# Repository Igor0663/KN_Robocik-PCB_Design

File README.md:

# KN_Robocik-PCB_Design
PCB projects and circuit schematics

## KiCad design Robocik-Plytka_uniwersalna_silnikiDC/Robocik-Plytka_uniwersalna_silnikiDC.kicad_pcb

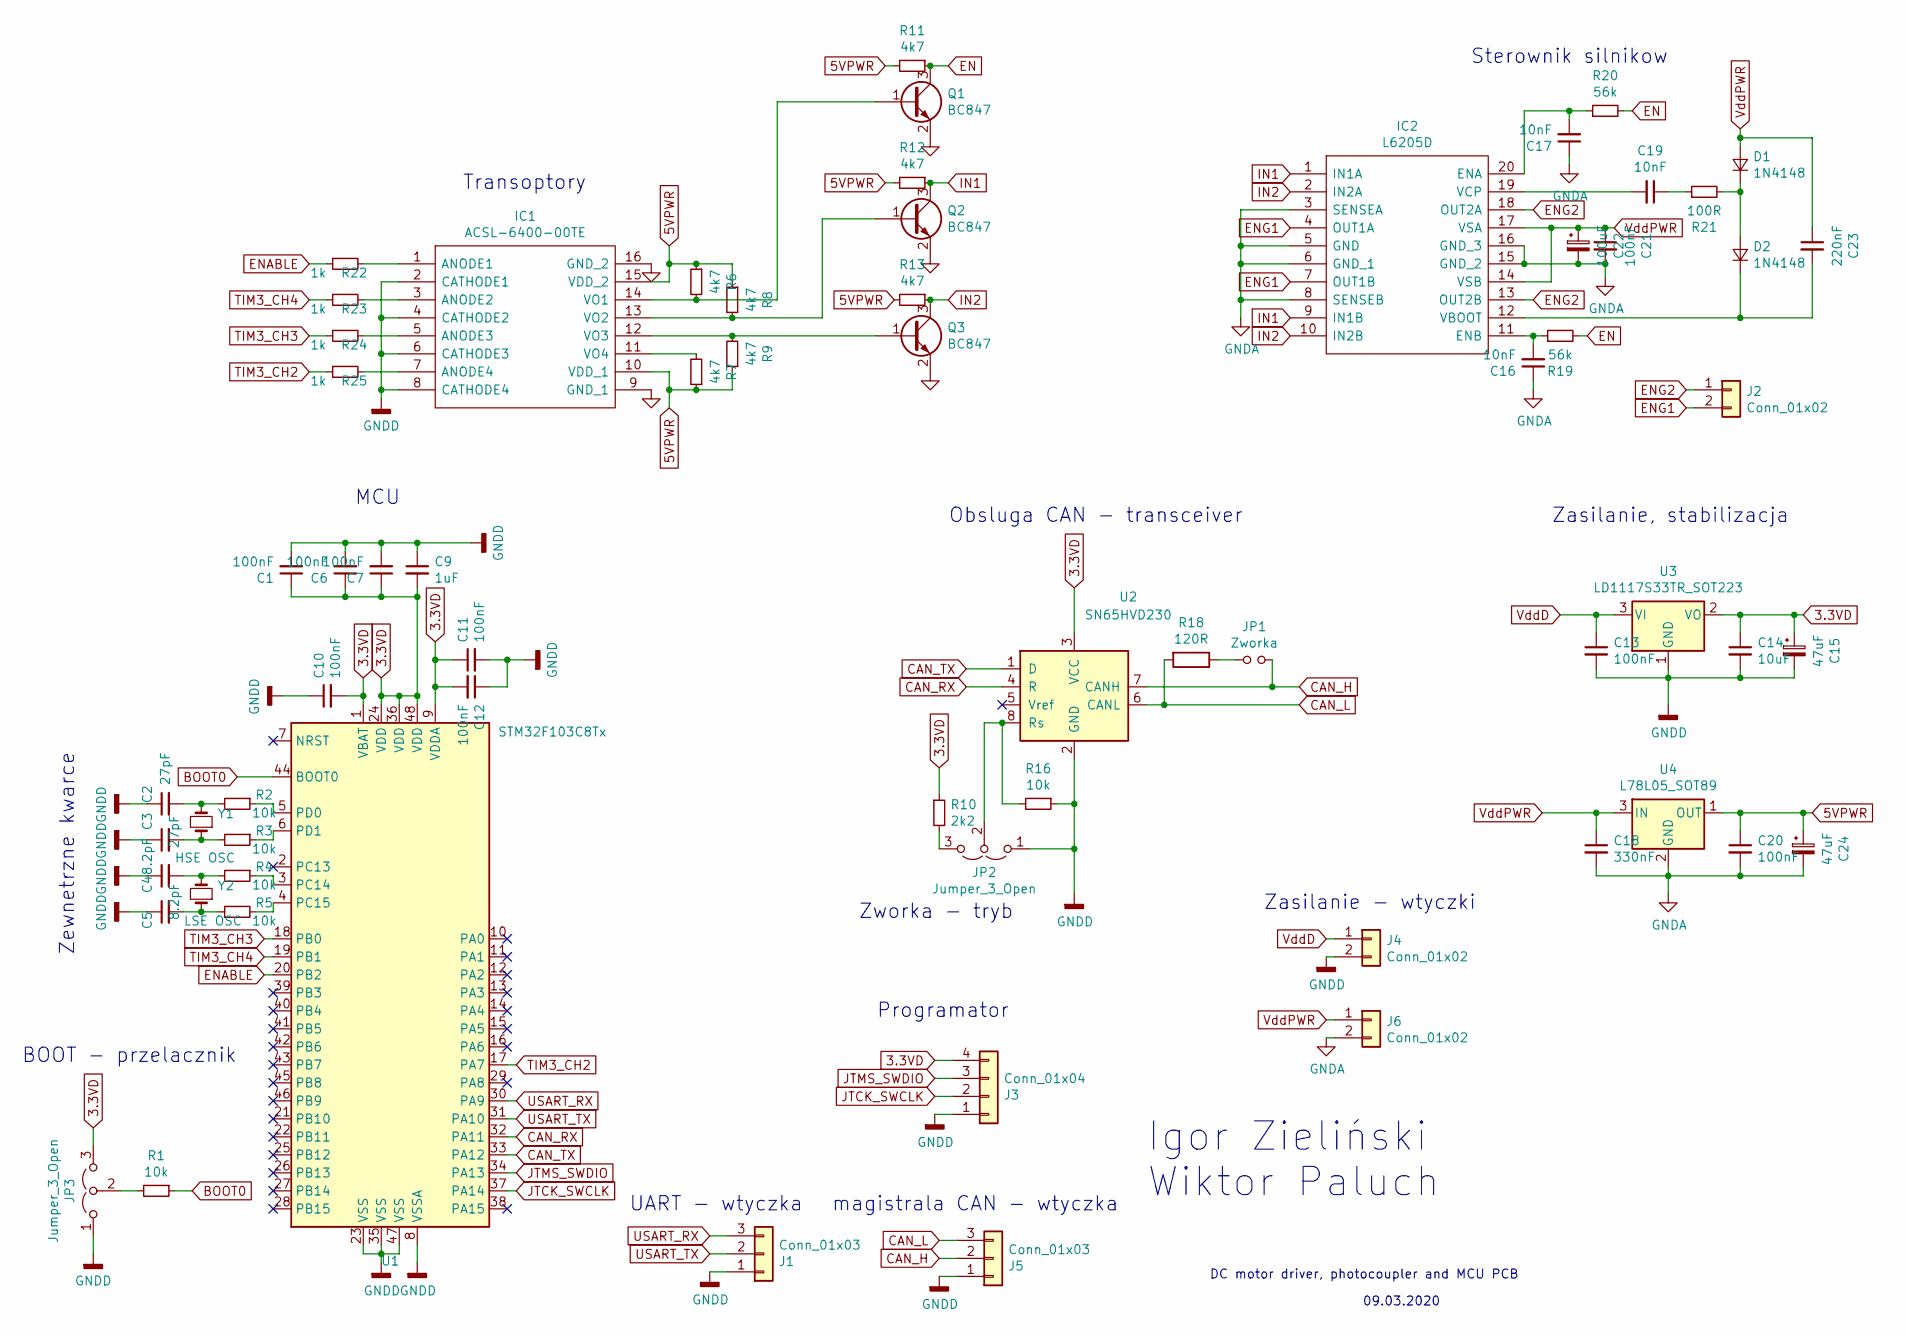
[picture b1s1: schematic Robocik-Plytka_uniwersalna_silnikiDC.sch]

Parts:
C1, C6, C7, C10, C11, C12, C13, C20, C21: 100nF; C_0805_2012Metric
C2, C3: 27pF; C_0805_2012Metric
C4, C5: 8.2pF; C_0805_2012Metric
C9: 1uF; C_0805_2012Metric
C14: 10uF; CP_EIA-6032-28_Kemet-C
C15, C24: 47uF; CP_EIA-6032-28_Kemet-C
C16, C17, C19: 10nF; C_0805_2012Metric
C18: 330nF; C_0805_2012Metric
C22: 100uF; CP_Elec_8x5.4
C23: 220nF; C_0805_2012Metric
D1, D2: 1N4148; D_SOD-123
IC1: ACSL-6400-00TE; SOP-16_4.55x10.3mm_P1.27mm; Mouser Part Number 630-ACSL-6400-00TE
IC2: L6205D; SO-20_12.8x7.5mm_P1.27mm; Manufacturer_Part_Number L6205D; Mouser Part Number 511-L6205D
J1: Conn_01x03; SHDR3W70P0X250_1X3_990X790X510P
J2: Conn_01x02; Molex_Mini-Fit_Jr_5569-02A2_2x01_P4.20mm_Horizontal
J3: Conn_01x04; 22-05-7045
J4: Conn_01x02; 43650-0214
J5: Conn_01x03; JST_PH_S3B-PH-K_1x03_P2.00mm_Horizontal
J6: Conn_01x02; Molex_Mini-Fit_Jr_5569-04A1_2x02_P4.20mm_Horizontal
JP1: Zworka; SolderJumper-2_P1.3mm_Open_Pad1.0x1.5mm
JP2, JP3: Jumper_3_Open; SolderJumper-3_P1.3mm_Open_Pad1.0x1.5mm_NumberLabels
Q1, Q2, Q3: BC847; SOT-23
R1, R2, R3, R4, R5, R16: 10k; R_0805_2012Metric
R6, R7, R8, R9, R11, R12, R13: 4k7; R_0805_2012Metric
R10: 2k2; R_0805_2012Metric
R18: 120R; R_0805_2012Metric
R19, R20: 56k; R_0805_2012Metric
R21: 100R; R_0805_2012Metric
R22, R23, R24, R25: 1k; R_0805_2012Metric
U1: STM32F103C8Tx; LQFP-48_7x7mm_P0.5mm
U2: SN65HVD230; SOIC-8_3.9x4.9mm_P1.27mm
U3: LD1117S33TR_SOT223; SOT-223-3_TabPin2
U4: L78L05_SOT89; SOT-89-3
Y1: HSE OSC; Crystal_SMD_5032-2Pin_5.0x3.2mm
Y2: LSE OSC; Crystal_SMD_3215-2Pin_3.2x1.5mm

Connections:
3.3VD: C1.1, C6.1, C7.1, C9.2, C10.2, C11.1, C12.2, C14.1, C15.1, J3.4, JP3.3 (B), R10.1, U1.1 (VBAT), U1.9 (VDDA), U1.24 (VDD), U1.36 (VDD), U1.48 (VDD), U2.3 (VCC), U3.2 (VO)
5VPWR: C20.1, C24.1, IC1.10 (VDD_1), IC1.15 (VDD_2), R6.1, R7.1, R8.1, R9.1, R11.2, R12.2, R13.2, U4.1 (OUT)
BOOT0: R1.1, U1.44 (BOOT0)
CAN_H: J5.2, JP1.2, U2.7 (CANH)
CAN_L: J5.3, R18.2, U2.6 (CANL)
CAN_RX: U1.32 (PA11), U2.4 (R)
CAN_TX: U1.33 (PA12), U2.1 (D)
EN: Q1.3 (C), R11.1, R19.2, R20.2
ENABLE: R22.1, U1.20 (PB2)
ENG1: IC2.4 (OUT1A), IC2.7 (OUT1B), J2.2
ENG2: IC2.13 (OUT2B), IC2.18 (OUT2A), J2.1
GNDA: C16.1, C17.1, C18.2, C20.2, C21.2, C22.2, C24.2, IC1.9 (GND_1), IC1.16 (GND_2), IC2.3 (SENSEA), IC2.5 (GND), IC2.6 (GND_1), IC2.8 (SENSEB), IC2.15 (GND_2), IC2.16 (GND_3), J6.2, Q1.2 (E), Q2.2 (E), Q3.2 (E), U4.2 (GND)
GNDD: C1.2, C2.1, C3.1, C4.1, C5.1, C6.2, C7.2, C9.1, C10.1, C11.2, C12.1, C13.2, C14.2, C15.2, IC1.2 (CATHODE1), IC1.4 (CATHODE2), IC1.6 (CATHODE3), IC1.8 (CATHODE4), J1.1, J3.1, J4.2, J5.1, JP2.1 (A), JP3.1 (A), R16.1, U1.8 (VSSA), U1.23 (VSS), U1.35 (VSS), U1.47 (VSS), U2.2 (GND), U3.1 (GND)
IN1: IC2.1 (IN1A), IC2.9 (IN1B), Q2.3 (C), R12.1
IN2: IC2.2 (IN2A), IC2.10 (IN2B), Q3.3 (C), R13.1
JTCK_SWCLK: J3.2, U1.37 (PA14)
JTMS_SWDIO: J3.3, U1.34 (PA13)
unnamed: C2.2, R2.2, Y1.2
unnamed: C3.2, R3.2, Y1.1
unnamed: C4.2, R4.2, Y2.2
unnamed: C5.2, R5.1, Y2.1
unnamed: C16.2, IC2.11 (ENB), R19.1
unnamed: C17.2, IC2.20 (ENA), R20.1
unnamed: C19.1, R21.1
unnamed: C19.2, IC2.19 (VCP)
unnamed: C23.2, D2.1 (K), IC2.12 (VBOOT)
unnamed: D1.1 (K), D2.2 (A), R21.2
unnamed: IC1.1 (ANODE1), R22.2
unnamed: IC1.3 (ANODE2), R23.2
unnamed: IC1.5 (ANODE3), R24.2
unnamed: IC1.7 (ANODE4), R25.2
unnamed: IC1.11 (VO4), R7.2
unnamed: IC1.12 (VO3), Q3.1 (B), R9.2
unnamed: IC1.13 (VO2), Q2.1 (B), R8.2
unnamed: IC1.14 (VO1), Q1.1 (B), R6.2
unnamed: JP1.1, R18.1
unnamed: JP2.2 (C), R16.2, U2.8 (Rs)
unnamed: JP2.3 (B), R10.2
unnamed: JP3.2 (C), R1.2
unnamed: R2.1, U1.5 (PD0)
unnamed: R3.1, U1.6 (PD1)
unnamed: R4.1, U1.3 (PC14)
unnamed: R5.2, U1.4 (PC15)
TIM3_CH2: R25.1, U1.17 (PA7)
TIM3_CH3: R24.1, U1.18 (PB0)
TIM3_CH4: R23.1, U1.19 (PB1)
USART_RX: J1.3, U1.30 (PA9)
USART_TX: J1.2, U1.31 (PA10)
VddD: C13.1, J4.1, U3.3 (VI)
VddPWR: C18.1, C21.1, C22.1, C23.1, D1.2 (A), IC2.14 (VSB), IC2.17 (VSA), J6.1, U4.3 (IN)

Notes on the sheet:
DC motor driver, photocoupler and MCU PCB
Igor Zieliński Wiktor Paluch
09.03.2020
BOOT - przelacznik
Obsluga CAN - transceiver
Programator
Zewnetrzne kwarce
Transoptory
Zworka - tryb
Zasilanie, stabilizacja
MCU
Sterownik silnikow
UART - wtyczka
magistrala CAN - wtyczka
Zasilanie - wtyczki

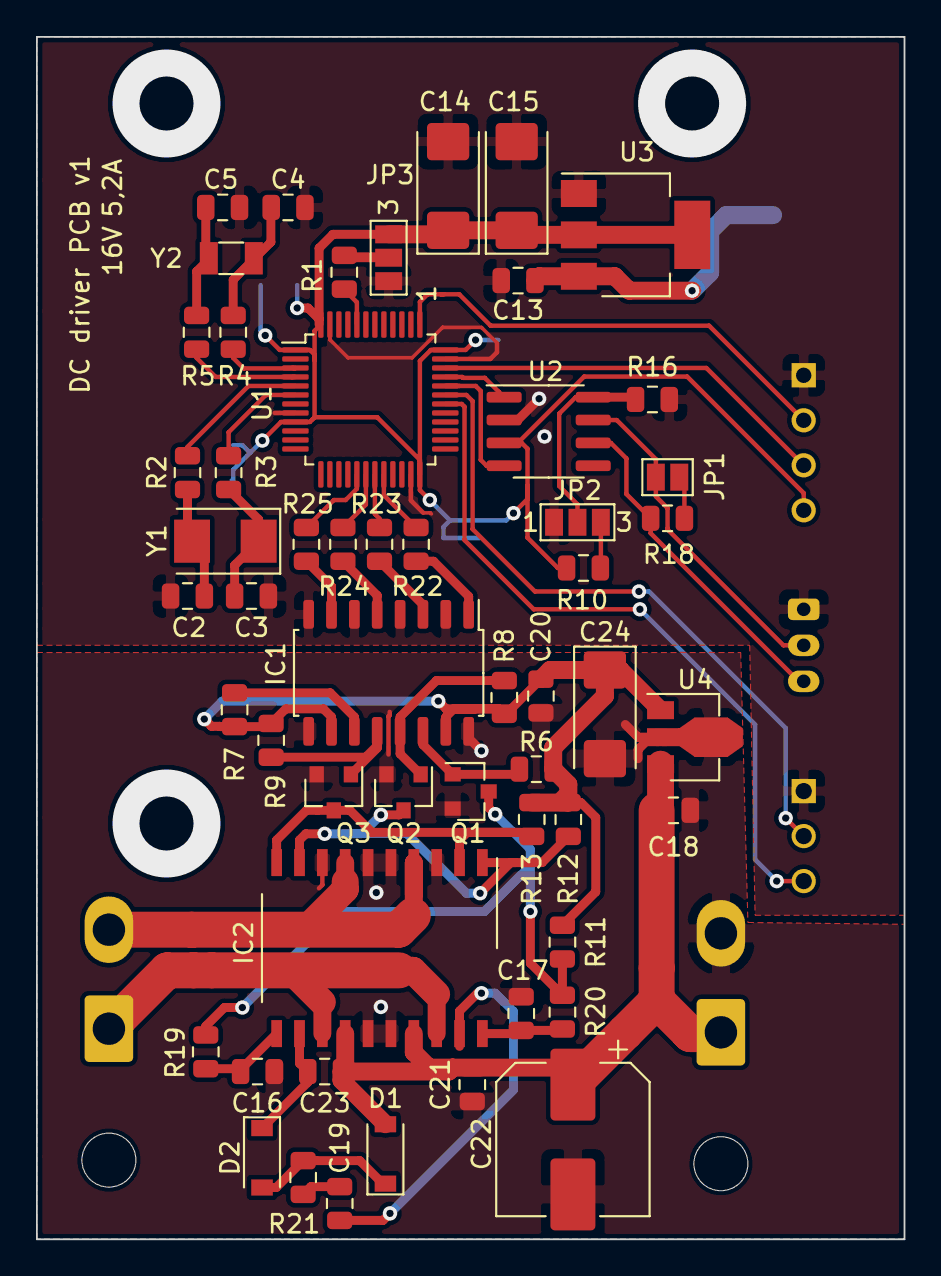
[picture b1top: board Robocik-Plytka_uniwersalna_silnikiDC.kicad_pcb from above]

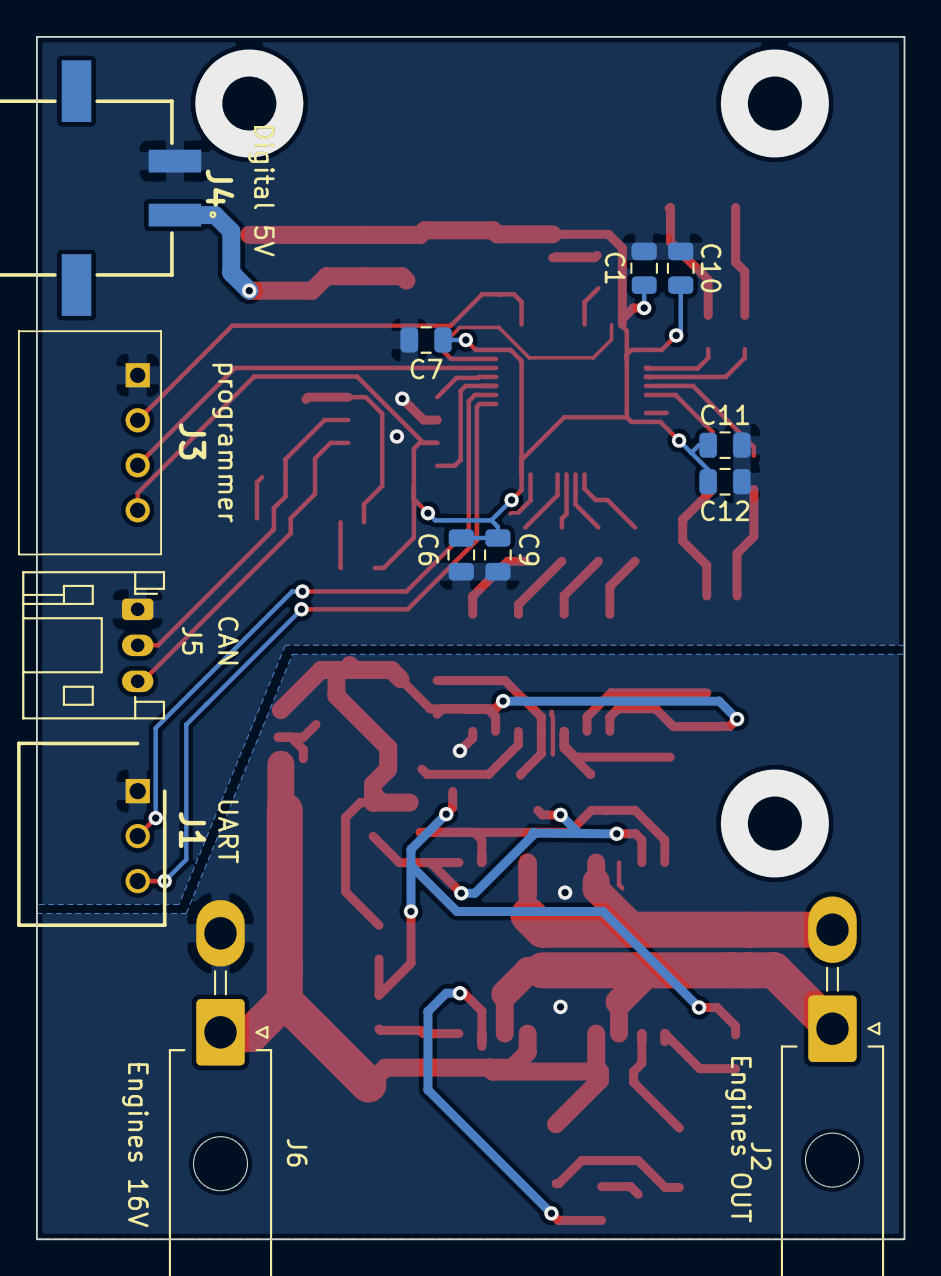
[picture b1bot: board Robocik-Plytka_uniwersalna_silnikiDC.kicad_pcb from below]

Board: 2 copper layers, 48.2 x 66.8 mm, 67 parts (13 on the bottom side), 50 nets.

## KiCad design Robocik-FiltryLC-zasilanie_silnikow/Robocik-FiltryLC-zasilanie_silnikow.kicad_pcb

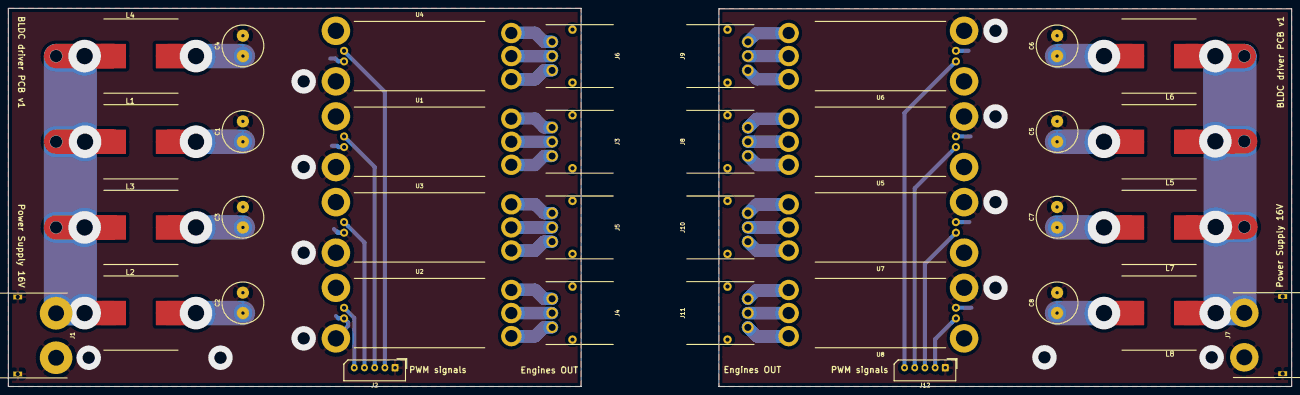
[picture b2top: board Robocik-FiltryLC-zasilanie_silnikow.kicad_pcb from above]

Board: 2 copper layers, 314.6 x 92.7 mm, 36 parts (0 on the bottom side), 43 nets.

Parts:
C1, C2, C3, C4, C5, C6, C7, C8: CP; C_Radial_D10.0mm_H20.0mm_P5.00mm
J1, J7: XT90PW-F
J2, J12: Conn_01x05; Molex_SPOX_5267-05A_1x05_P2.50mm_Vertical
J3, J4, J5, J6, J8, J9, J10, J11: Conn_01x03; MR30PW-FB
L1, L2, L3, L4, L5, L6, L7, L8: L; WE-HCI_189023
U1, U2, U3, U4, U5, U6, U7, U8: ESC

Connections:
GND: C1.2, C2.2, C3.2, C4.2, C5.2, C6.2, C7.2, C8.2, J1.2, J1.3, J1.4, J2.1, J7.1, J7.3, J7.4, J12.1, U1.2, U1.4, U2.2, U2.4, U3.2, U3.4, U4.2, U4.4, U5.2, U5.4, U6.2, U6.4, U7.2, U7.4, U8.2, U8.4
unnamed: C1.1, L1.2, U1.1
unnamed: C2.1, L2.2, U2.1
unnamed: C3.1, L3.2, U3.1
unnamed: C4.1, L4.2, U4.1
unnamed: C5.1, L5.2, U5.1
unnamed: C6.1, L6.2, U6.1
unnamed: C7.1, L7.2, U7.1
unnamed: C8.1, L8.2, U8.1
unnamed: J1.1, L1.1, L2.1, L3.1, L4.1
unnamed: J2.2, U4.3
unnamed: J2.4, U3.3
unnamed: J2.5, U2.3
unnamed: J2.3, U1.3
unnamed: J3.1, U1.7
unnamed: J3.2, U1.6
unnamed: J3.3, U1.5
unnamed: J4.1, U2.7
unnamed: J4.2, U2.6
unnamed: J4.3, U2.5
unnamed: J5.1, U3.7
unnamed: J5.2, U3.6
unnamed: J5.3, U3.5
unnamed: J6.1, U4.7
unnamed: J6.2, U4.6
unnamed: J6.3, U4.5
unnamed: J7.2, L5.1, L6.1, L7.1, L8.1
unnamed: J8.1, U5.7
unnamed: J8.2, U5.6
unnamed: J8.3, U5.5
unnamed: J9.1, U6.7
unnamed: J9.2, U6.6
unnamed: J9.3, U6.5
unnamed: J10.1, U7.7
unnamed: J10.2, U7.6
unnamed: J10.3, U7.5
unnamed: J11.1, U8.7
unnamed: J11.2, U8.6
unnamed: J11.3, U8.5
unnamed: J12.2, U8.3
unnamed: J12.3, U7.3
unnamed: J12.5, U6.3
unnamed: J12.4, U5.3

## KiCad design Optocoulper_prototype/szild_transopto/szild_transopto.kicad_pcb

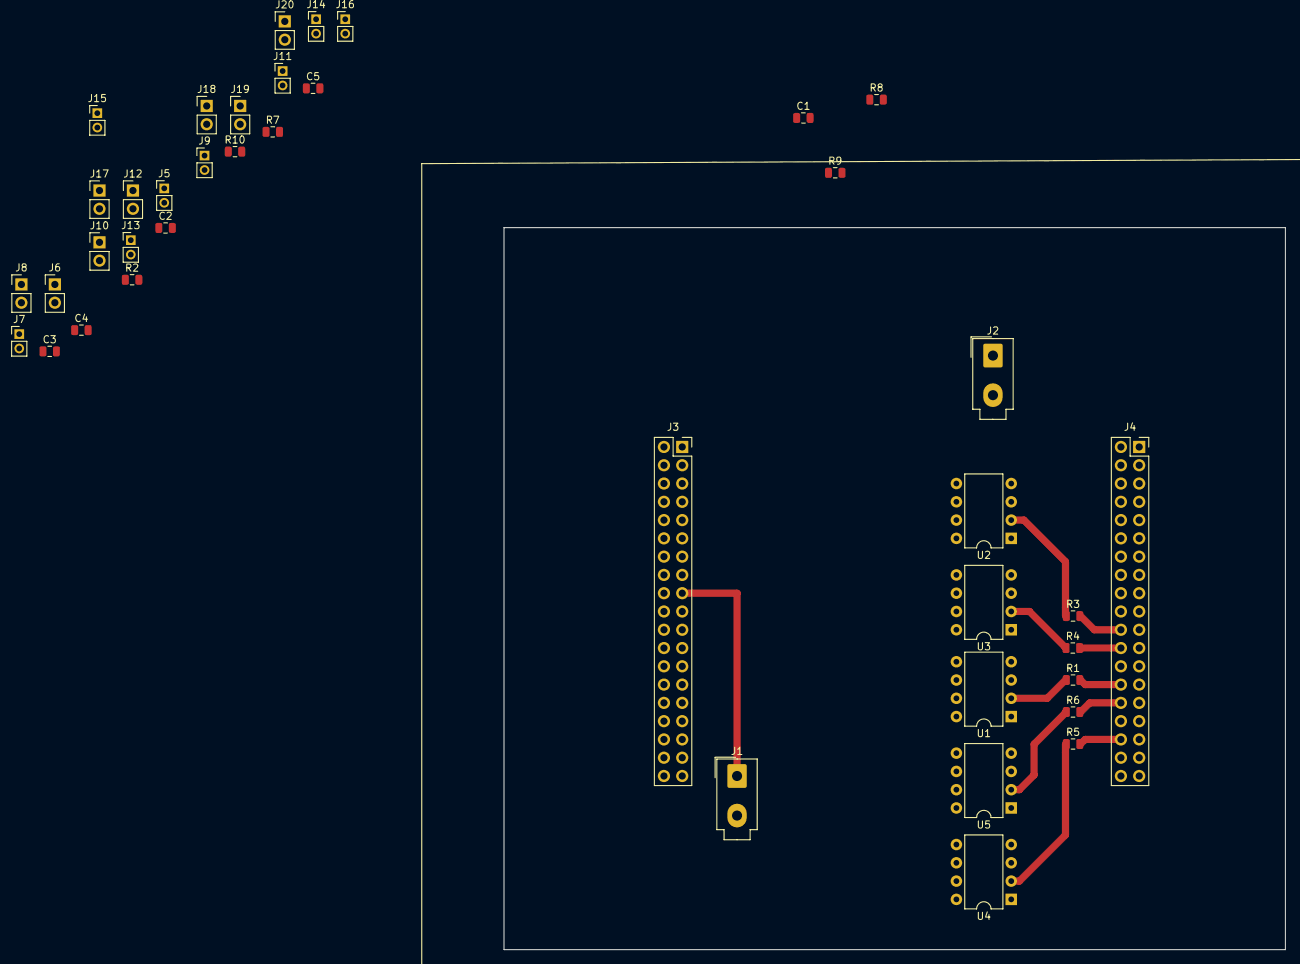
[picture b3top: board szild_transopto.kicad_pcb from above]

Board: 2 copper layers, 108.6 x 100.3 mm, 40 parts (0 on the bottom side), 19 nets.

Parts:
C1, C2, C3, C4, C5: 10n; C_0805_2012Metric
J1: Zasilanie_wejść; Molex_Mini-Fit_Jr_5566-02A_2x01_P4.20mm_Vertical
J2: Zasilanie_wyjść; Molex_Mini-Fit_Jr_5566-02A_2x01_P4.20mm_Vertical
J3: Header_left; PinSocket_2x19_P2.54mm_Vertical
J4: Header_right; PinSocket_2x19_P2.54mm_Vertical
J5: Z1_2_0; PinHeader_1x02_P2.00mm_Vertical
J6: Z1; PinHeader_1x02_P2.54mm_Vertical
J7: Z2_2_0; PinHeader_1x02_P2.00mm_Vertical
J8: Z2; PinHeader_1x02_P2.54mm_Vertical
J9: Z3_2_0; PinHeader_1x02_P2.00mm_Vertical
J10: Z3; PinHeader_1x02_P2.54mm_Vertical
J11: Z4_2_0; PinHeader_1x02_P2.00mm_Vertical
J12: Z4; PinHeader_1x02_P2.54mm_Vertical
J13: LP_2_0; PinHeader_1x02_P2.00mm_Vertical
J14: PP_2_0; PinHeader_1x02_P2.00mm_Vertical
J15: LT_2_0; PinHeader_1x02_P2.00mm_Vertical
J16: PT_2_0; PinHeader_1x02_P2.00mm_Vertical
J17: LP; PinHeader_1x02_P2.54mm_Vertical
J18: PP; PinHeader_1x02_P2.54mm_Vertical
J19: LT; PinHeader_1x02_P2.54mm_Vertical
J20: PT; PinHeader_1x02_P2.54mm_Vertical
R1, R3, R4, R5, R6: 470R; R_0805_2012Metric
R2, R7, R8, R9, R10: 4k7; R_0805_2012Metric
U1, U2, U3, U4, U5: 6N137; DIP-8_W7.62mm

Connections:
+5V: C1.1, C2.1, C3.1, C4.1, C5.1, J2.1, R2.1, R7.1, R8.1, R9.1, R10.1, U1.7, U1.8, U2.7, U2.8, U3.7, U3.8, U4.7, U4.8, U5.7, U5.8
/TIM1_1-LP: J4.24, R4.2
/TIM1_2-PP: J4.22, R3.2
/TIM1_3-LT: J4.34, R5.2
/TIM3_1-PT: J4.30, R6.2
/TIM3_2-Z: J4.28, R1.2
GND: J1.2, J3.19, U1.3, U2.3, U3.3, U4.3, U5.3
GNDD: C1.2, C2.2, C3.2, C4.2, C5.2, J2.2, J5.2, J6.2, J7.2, J8.2, J9.2, J10.2, J11.2, J12.2, J13.2, J14.2, J15.2, J16.2, J17.2, J18.2, J19.2, J20.2, U1.5, U2.5, U3.5, U4.5, U5.5
unnamed: J5.1, J6.1, J7.1, J8.1, J9.1, J10.1, J11.1, J12.1, R2.2, U1.6
unnamed: J13.1, J17.1, R8.2, U3.6
unnamed: J14.1, J18.1, R7.2, U2.6
unnamed: J15.1, J19.1, R9.2, U4.6
unnamed: J16.1, J20.1, R10.2, U5.6
unnamed: R1.1, U1.2
unnamed: R3.1, U2.2
unnamed: R4.1, U3.2
unnamed: R5.1, U4.2
unnamed: R6.1, U5.2
VCC: J1.1, J3.17

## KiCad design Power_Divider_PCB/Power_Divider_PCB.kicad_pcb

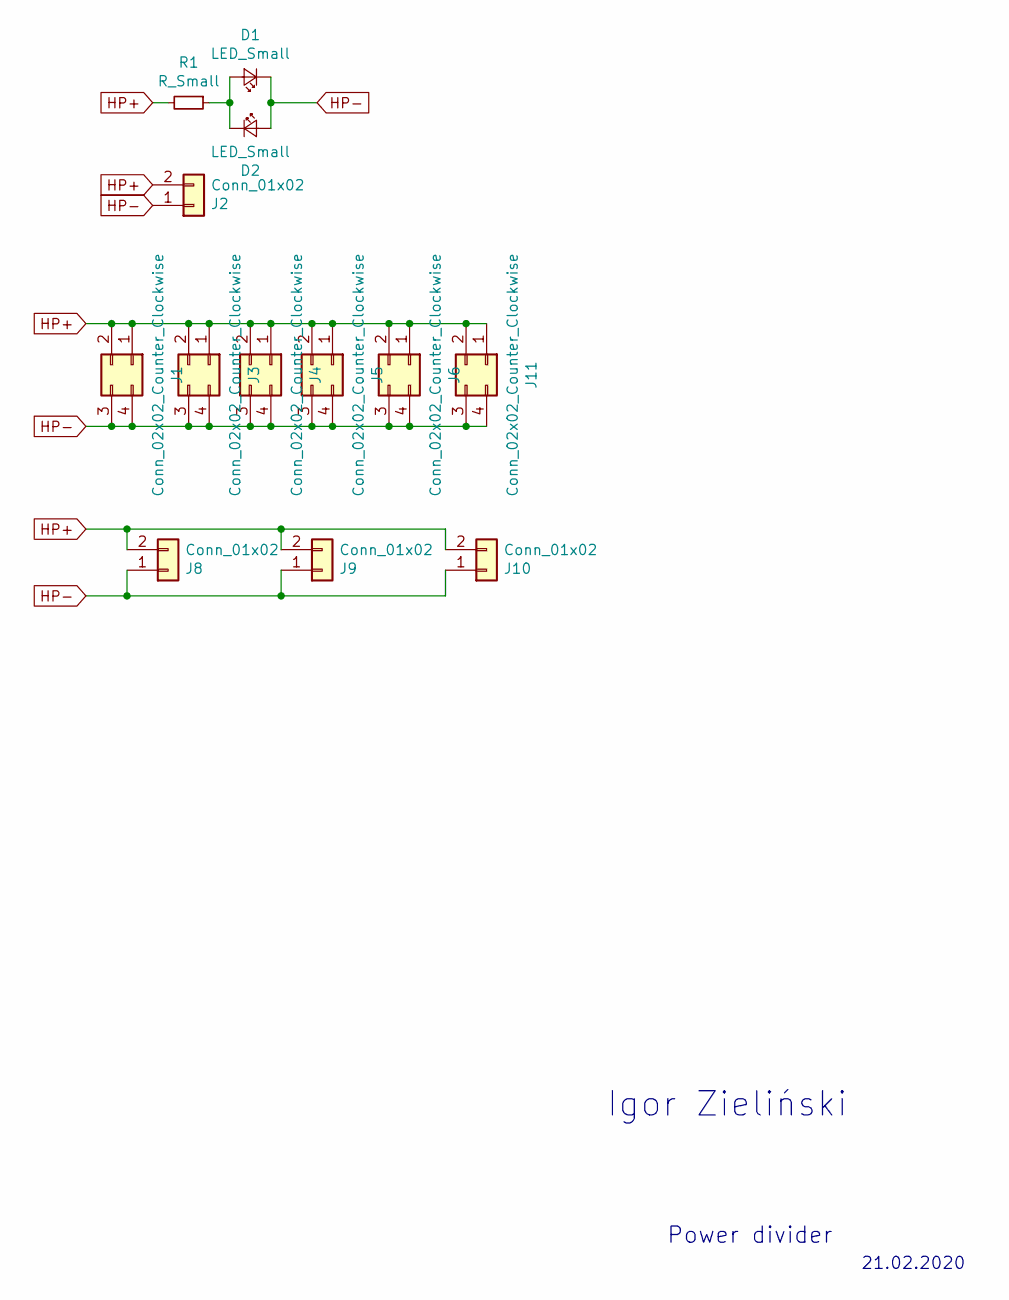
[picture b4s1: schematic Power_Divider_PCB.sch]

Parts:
D1, D2: LED_Small; LED_D3.0mm
J1, J3, J4, J5, J6, J11: Conn_02x02_Counter_Clockwise; Molex_Mini-Fit_Jr_5566-04A_2x02_P4.20mm_Vertical
J2, J8, J9, J10: Conn_01x02; XT90PW-F
R1: R_Small; R_Axial_DIN0207_L6.3mm_D2.5mm_P7.62mm_Horizontal

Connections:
HP+: J1.1, J1.2, J2.2, J3.1, J3.2, J4.1, J4.2, J5.1, J5.2, J6.1, J6.2, J8.2, J9.2, J10.2, J11.1, J11.2, R1.2
HP-: D1.1 (K), D2.2 (A), J1.3, J1.4, J2.1, J3.3, J3.4, J4.3, J4.4, J5.3, J5.4, J6.3, J6.4, J8.1, J9.1, J10.1, J11.3, J11.4
unnamed: D1.2 (A), D2.1 (K), R1.1

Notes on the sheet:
Power divider
21.02.2020
Igor Zieliński

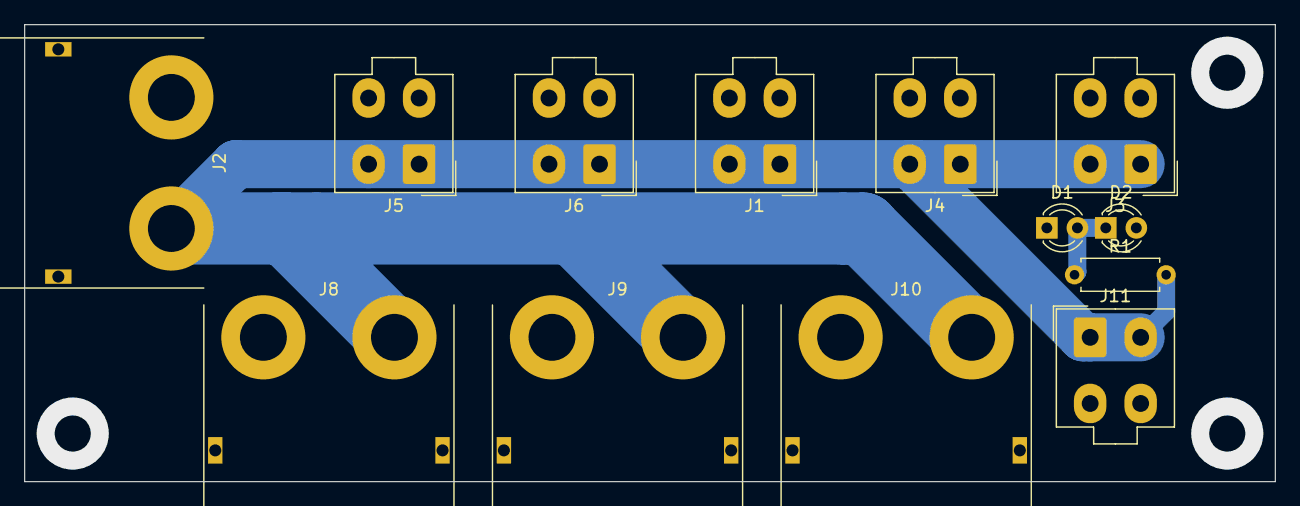
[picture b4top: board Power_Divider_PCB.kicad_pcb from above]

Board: 2 copper layers, 104.0 x 38.0 mm, 13 parts (0 on the bottom side), 3 nets.

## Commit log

2020-02-13 Driver + optocoupler wiring, added linear regulators for power and digital power supply
2020-02-13 Added tantalum capacitors on the output of linear regulators, removed second photocoupler and simplified flags. Removed jumpers. Fixed RC filters on ENABLE pins.
2020-02-14 finised project added
2020-02-15 Added JTAG connector, power supply, MCU connection
2020-02-15 Added CAN transceiver schematic, Boot and LSE/OSC oscillator schematic, updated drawing. Added MCU pinout from STM32CubeMX
2020-02-15 Changed transceiver ground to digital, fixed power ground labelson driver ground, added footprints for capacitors and resistors.
2020-02-15 Updated circuit pdf
2020-02-19 Schematic: Changed programming from JTAG to SWD. Added solderbridges. Added timers and their connections with optocoupler. Corrected minor mistakes. PCB: First version: organised elements, most conne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
2020-02-21 Power divider project - first design
2020-02-21 Added one extra XT connector, moved existing molexes. Added Voltage polarization check: green LED - OK, red LED - wrong.
2020-02-22 Updated circuit pdf and pcb renders.
2020-02-23 Changed power supply line on schematic, added missing connections on PCB layout, added second layer connections and vias. Added layout drawing and updated schematic drawing
2020-02-23 Corrected GNDA and GNDD at MCU on schematic. Changed passive elements footprints from 1206 to 0805. Corrected input capacitors placement and transoptors placement. Corrected many connections on PCB. 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
2020-02-25 Added footprints for all connectors. Moved decoupling capacitors next to engine driver. Fixed minor mistakes on PCB layout.
2020-02-25 Fixed power supply decoupling capacitors placement on PCB layout.
2020-02-26 Piękna płytka z transoptorami - dla korzyści przyszłych pokoleń
2020-02-26 Changed placements of elements, added GNDA vias, updated elements designations on PCB (not finished)
2020-02-26 Added second board. Added 3D models to most elements. Included PCB top and botton jpg files. Resized PCB - from 12 x 17 cm to 10,5 x 12,5cm.
2020-02-27 Added 3D model to all connectors, fixed some connections on PCB. Added ground layers for both GNDA and GNDD.
2020-02-27 Updated circuit schematic, layout pdf. Added pcb views: top and bottom.
2020-02-28 Moved all connectors to the same side of PCB. Redesigned ground planes. Added folder "quick view" which consists of PCB schematic, layout, jpegs of PCB top and bottom side and new added step 3D model.
2020-02-28 Added folders for footprints and libraries. Added STM pin configuration to quick view folder
2020-03-01 Moved power connector to the side of the board. Added wiring for ESC output. Removed soldermask layers from high power lines.
2020-03-01 Added mounting screws for bus bars. Increased size of power+ bus bar copper layer.
2020-03-01 Addeed additional mounting screws for bus bars.
2020-03-04 Added connectors description on board.
2020-03-04 PCB top JPEG update
2020-03-04 Added connector and PCB labels on board.
2020-03-06 Added missing 3D model for optocoupler. Moved all connector to the other side of the board. Reduced PCB size.
2020-03-06 Further reduce of PCB size - moved description of every connector away from the border of PCB.
2020-03-06 Fixed size of LSE crystal oscilator. Added 3D models for LSE and HSE oscilators.
2020-03-09 Added capacitors values for crystals. Redesigned low-pass filters at EN pins of driver: changed R and C values.
2020-03-09 fixed gnda layer
2020-03-12 Reduced size of a board, added mounting holes and description of max current and voltage
